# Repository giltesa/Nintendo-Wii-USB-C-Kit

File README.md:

# Nintendo Wii / Wii Mini / Wii U: USB-C Kit

The **Nintendo Wii: USB-C Kit** is a board that allows to replace the original power connector for a modern and standard USB-C.

**If your original connector / power supply is too old or damaged** and you need a new one, or **if you would like to power up your Nintendo Wii with a standard USB-C PD charger**, such as the charger for your phone, or laptop, you can do so with this kit.

This board is compatible with these three models:

*   Nintendo Wii
*   Nintendo Wii Mini
*   Nintendo Wii U

## HOW DOES IT WORK?

The **USB-C Power Delivery technology** (**USB-C PD**) allows for communication between the device and the power supply(charger), enabling the negotiation of the voltage to be supplied through the USB-C cable. In this case, the microchip included on this board is configured to request 12v or 15v(1), signaling to the charger that it requires 12v or 15v(1) to run on. If the charger is compatible, it will supply the requested voltage. If it’s not compatible, nothing will happen, and the Nintendo Wii won’t power on.

 **(1)** The circuit has a selection jumper; if you solder it in one position, the circuit will require 12v, and if you solder it in the other position, it will require 15v from the power supply.

## Would you like it?

[**Nintendo Wii: USB-C Kit**](https://shop.giltesa.com/?p=2794)

## License

This project is licensed under a **Creative Commons** license:
**[Attribution-NonCommercial-ShareAlike 4.0 International (CC BY-NC-SA 4.0) ](https://creativecommons.org/licenses/by-nc-sa/4.0/)**

Check the [LICENSE.md](LICENSE.md) for more information.

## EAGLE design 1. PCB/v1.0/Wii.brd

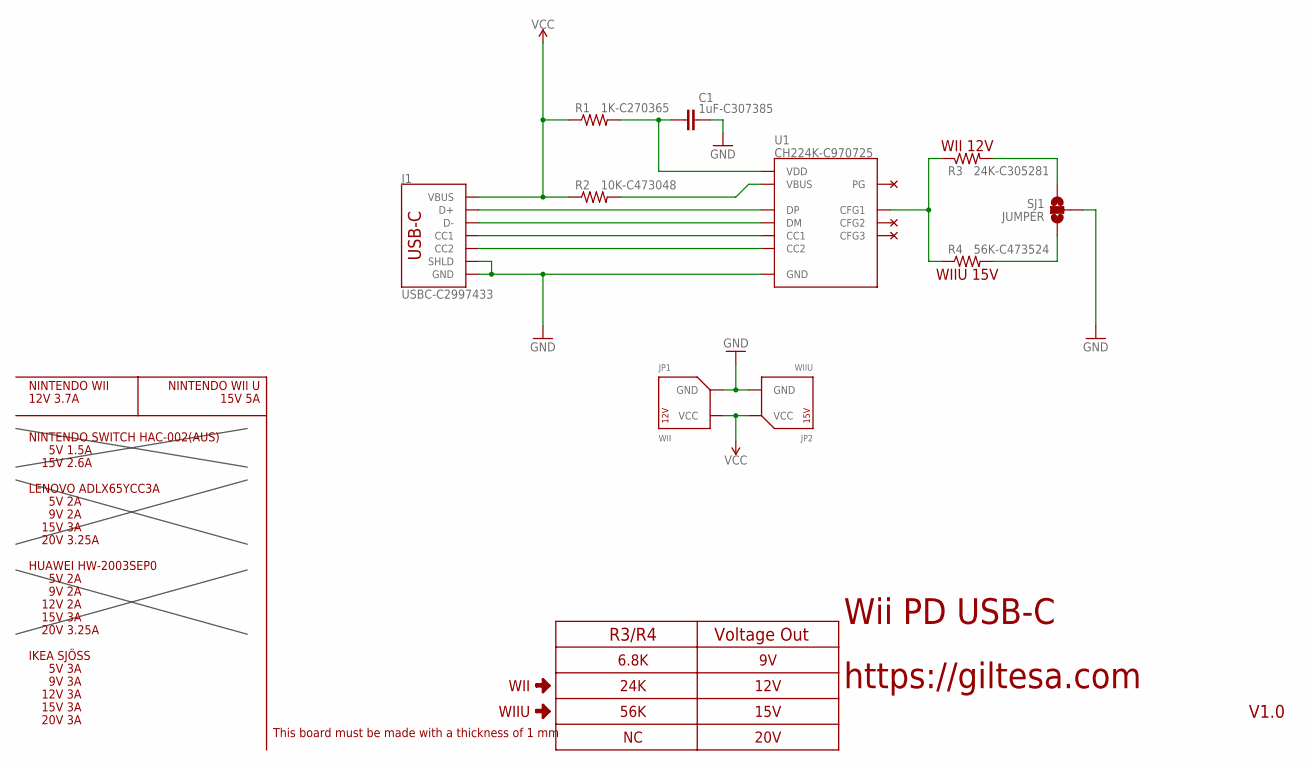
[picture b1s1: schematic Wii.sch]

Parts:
C1: 1uF-C307385; C0201
J1: USBC-C2997433; USB-C_16P
JP1: WII; WII_1X02
JP2: WIIU; WIIU_1X02
R1: 1K-C270365; R0201
R2: 10K-C473048; R0201
R3: 24K-C305281; R0201
R4: 56K-C473524; R0201
SJ1: JUMPER; JUMPER-SMD-3_NO_SILK
U1: CH224K-C970725; ESSOP10

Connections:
CC1: J1.A5-CC1 (CC1), U1.7 (CC1)
CC2: J1.B5-CC2 (CC2), U1.6 (CC2)
D+: J1.A6-DP1 (D+), J1.B6-DP2 (D+), U1.4 (DP)
D-: J1.A7-DN1 (D-), J1.B7-DN2 (D-), U1.5 (DM)
GND: C1.2, J1.GND1 (GND), J1.GND2 (GND), J1.SHLD1 (SHLD), J1.SHLD2 (SHLD), J1.SHLD3 (SHLD), J1.SHLD4 (SHLD), JP1.GND1 (GND), JP2.GND1 (GND), SJ1.2, U1.0 (GND)
unnamed: R3.2, SJ1.1
unnamed: R3.1, R4.1, U1.9 (CFG1)
unnamed: R4.2, SJ1.3
unnamed: R2.2, U1.8 (VBUS)
VCC: J1.VBUS1 (VBUS), J1.VBUS2 (VBUS), JP1.VCC1 (VCC), JP2.VCC1 (VCC), R1.1, R2.1
VDD: C1.1, R1.2, U1.1 (VDD)

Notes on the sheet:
Wii PD USB-C
https://giltesa.com
V1.0
This board must be made with a thickness of 1 mm
NINTENDO SWITCH HAC-002(AUS)
5V 1.5A
15V 2.6A
HUAWEI HW-2003SEP0
5V 2A
9V 2A
12V 2A
15V 3A
20V 3.25A
NINTENDO WII
12V 3.7A
R3/R4
Voltage Out
6.8K
24K
56K
12V
15V
20V
LENOVO ADLX65YCC3A
IKEA SJÖSS
5V 3A
9V 3A
12V 3A
20V 3A
WII
WIIU
WII 12V
WIIU 15V
NINTENDO WII U
15V 5A

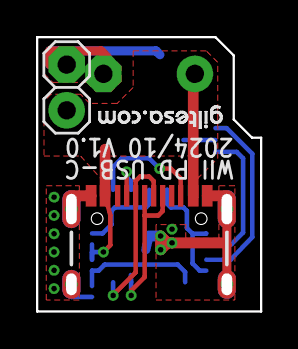
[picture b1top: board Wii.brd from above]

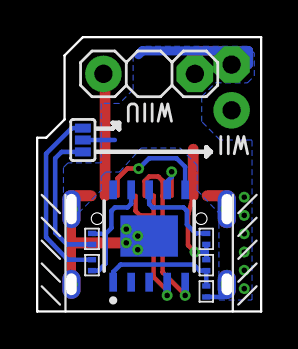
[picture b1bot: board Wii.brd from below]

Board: 2 copper layers, 12.4 x 15.2 mm, 11 parts (8 on the bottom side), 11 nets.

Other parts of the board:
U$28: GILTESA.COM_7MM_MASK

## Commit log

2024-10-12 no message
2025-08-01 v1.0

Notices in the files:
parts and their libraries:
SparkFun: Licensing: CC v3.0 Share-Alike You are welcome to use this library for commercial purposes.
SparkFun-PowerSymbols: Licensing: Creative Commons ShareAlike 4.0 International - https://creativecommons.org/licenses/by-sa/4.0
